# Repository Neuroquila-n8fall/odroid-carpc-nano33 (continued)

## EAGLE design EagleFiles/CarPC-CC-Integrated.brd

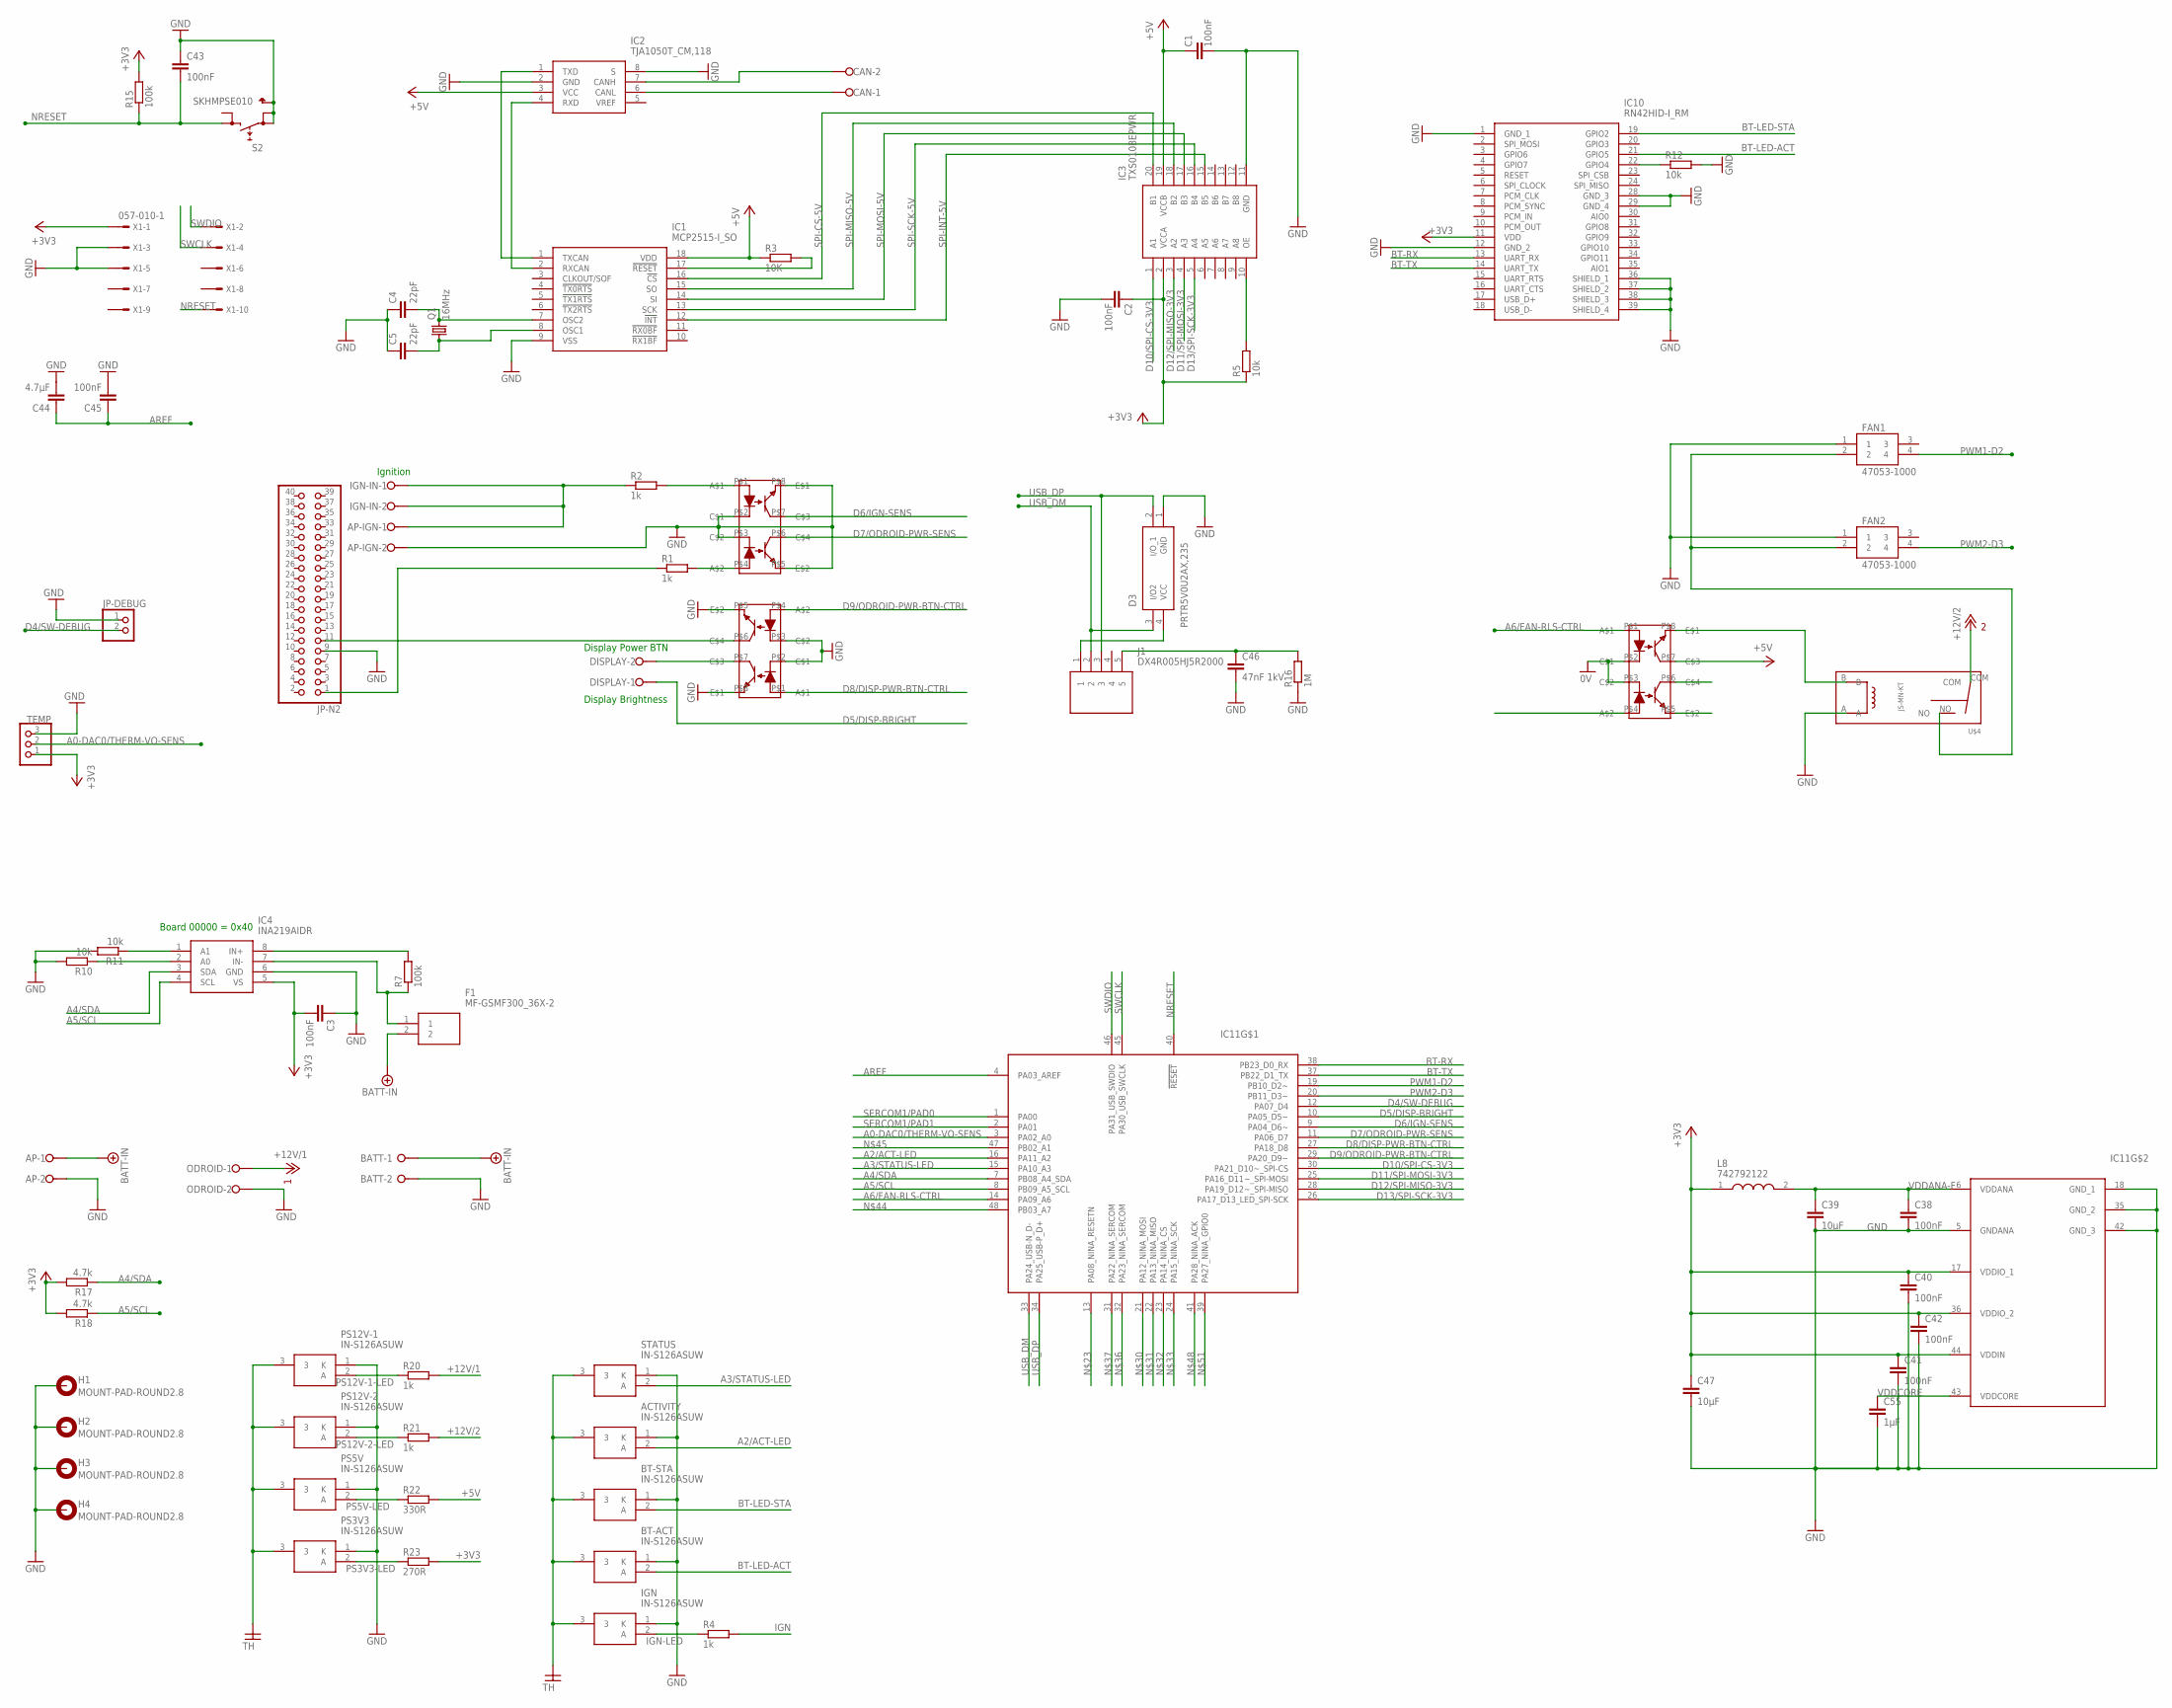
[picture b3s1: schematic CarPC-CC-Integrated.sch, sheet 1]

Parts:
ACTIVITY: IN-S126ASUW; INS126ASUW
AP: W237-02P; W237-132
AP-IGN: W237-02P; W237-132
BATT: W237-02P; W237-132
BT-ACT: IN-S126ASUW; INS126ASUW
BT-STA: IN-S126ASUW; INS126ASUW
C1, C2, C3, C38, C40, C41, C42, C43, C45: 100nF; C1206
C4, C5: 22pF; C1206
C39, C47: 10µF; C1206
C44: 4.7µF; C1206
C46: 47nF 1kV; C1206
C55: 1µF; C1206
CAN: W237-02P; W237-132
D3: PRTR5V0U2AX,235; PESD2ETHAXR
DISPLAY: W237-02P; W237-132
F1: MF-GSMF300_36X-2; MFGSMF30036X2
FAN1, FAN2: 47053-1000
H1, H2, H3, H4: MOUNT-PAD-ROUND2.8; 2,8-PAD
IC1: MCP2515-I_SO; SOIC127P1030X265-18N
IC2: TJA1050T_CM,118; SOIC127P600X175-8N
IC3: TXS0108EPWR; SOP65P640X120-20N
IC4: INA219AIDR; SOIC127P600X175-8N
IC10: RN42HID-I_RM; RN42HIDIRM
IC11: ATSAMD21G18A-AU-SPLIT; QFP50P900X900X120-48N
IGN: IN-S126ASUW; INS126ASUW
IGN-IN: W237-02P; W237-132
J1: DX4R005HJ5R2000; DX4R005HJ5
JP-DEBUG: PINHD-1X2; 1X02
JP-N2: PINHD-2X20; 2X20
L8: 742792122; INDC3216X130N
ODROID: W237-02P; W237-132
OK-FAN-CTRL: ILD74; FPR_ILD74
OK-PWR-IGN: ILD74; FPR_ILD74
OK-PWR-N2_DISP: ILD74; FPR_ILD74
PS3V3, PS5V, PS12V-1, PS12V-2: IN-S126ASUW; INS126ASUW
Q1: 16MHz; HC49/S
R1, R2, R4, R20, R21: 1k; R1206
R3: 10K; R1206
R5, R10, R11, R12: 10k; R1206
R7, R15: 100k; R1206
R16: 1M; R1206
R17, R18: 4.7k; R1206
R22: 330R; R1206
R23: 270R; R1206
S2: SKHMPSE010; SKHMPXE010
STATUS: IN-S126ASUW; INS126ASUW
TEMP: PINHD-1X3/90; 1X03/90
U$4: JS-MN-KT; FPR_JS-MN-KT
X1: 057-010-1

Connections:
0V: OK-FAN-CTRL.P$2, OK-FAN-CTRL.P$3
+3V3: C2.1, C3.2, C40.1, C41.1, C42.1, C47.1, IC3.2 (VCCA), IC4.5 (VS), IC10.11 (VDD), IC11.17 (VDDIO_1), IC11.36 (VDDIO_2), IC11.44 (VDDIN), L8.1, R5.1, R15.2, R17.2, R18.2, R23.2, TEMP.1, X1.1; also elsewhere on the board
+5V: C1.1, IC1.18 (VDD), IC2.3 (VCC), IC3.19 (VCCB), OK-FAN-CTRL.P$7, R3.1, R22.2; also elsewhere on the board
+12V/1: ODROID.1, R20.2; also elsewhere on the board
+12V/2: R21.2, U$4.COM; also elsewhere on the board
A0-DAC0/THERM-VO-SENS: IC11.3 (PA02_A0), TEMP.2
A2/ACT-LED: ACTIVITY.2 (A), IC11.16 (PA11_A2)
A3/STATUS-LED: IC11.15 (PA10_A3), STATUS.2 (A)
A4/SDA: IC4.3 (SDA), IC11.7 (PB08_A4_SDA), R17.1
A5/SCL: IC4.4 (SCL), IC11.8 (PB09_A5_SCL), R18.1
A6/FAN-RLS-CTRL: IC11.14 (PA09_A6), OK-FAN-CTRL.P$1
AREF: C44.1, C45.1, IC11.4 (PA03_AREF)
BATT-IN: AP.1, BATT.1, F1.2; also elsewhere on the board
BATT-IN-FUSED: F1.1, IC4.7 (IN-), R7.1
BT-ACTIVATE: IC10.22 (GPIO4), R12.1
BT-LED-ACT: BT-ACT.2 (A), IC10.21 (GPIO5)
BT-LED-STA: BT-STA.2 (A), IC10.19 (GPIO2)
BT-RX: IC10.13 (UART_RX), IC11.38 (PB23_D0_RX)
BT-TX: IC10.14 (UART_TX), IC11.37 (PB22_D1_TX)
CAN-H: CAN.2, IC2.7 (CANH)
CAN-L: CAN.1, IC2.6 (CANL)
D4/SW-DEBUG: IC11.12 (PA07_D4), JP-DEBUG.2
D5/DISP-BRIGHT: DISPLAY.1, IC11.10 (PA05_D5~)
D6/IGN-SENS: IC11.9 (PA04_D6~), OK-PWR-IGN.P$7
D7/ODROID-PWR-SENS: IC11.11 (PA06_D7), OK-PWR-IGN.P$6
D8/DISP-PWR-BTN-CTRL: IC11.27 (PA18_D8), OK-PWR-N2_DISP.P$1
D9/ODROID-PWR-BTN-CTRL: IC11.29 (PA20_D9~), OK-PWR-N2_DISP.P$4
D10/SPI-CS-3V3: IC3.1 (A1), IC11.30 (PA21_D10~_SPI-CS)
D11/SPI-MOSI-3V3: IC3.4 (A3), IC11.25 (PA16_D11~_SPI-MOSI)
D12/SPI-MISO-3V3: IC3.3 (A2), IC11.28 (PA19_D12~_SPI-MISO)
D13/SPI-SCK-3V3: IC3.5 (A4), IC11.26 (PA17_D13_LED_SPI-SCK)
DISP-PWR-BTN: DISPLAY.2, OK-PWR-N2_DISP.P$7
FAN-12V: FAN1.2, FAN2.2, U$4.NO
FAN-RLS-TRIG: OK-FAN-CTRL.P$8, U$4.B
GND: ACTIVITY.1 (K), AP.2, AP-IGN.2, BATT.2, BT-ACT.1 (K), BT-STA.1 (K), C1.2, C2.2, C3.1, C4.1, C5.1, C38.2, C39.2, C40.2, C41.2, C42.2, C43.1, C44.2, C45.2, C46.2, C47.2, C55.2, D3.1 (GND), FAN1.1, FAN2.1, H1.B2,8, H2.B2,8, H3.B2,8, H4.B2,8, IC1.9 (VSS), IC2.2 (GND), IC2.8 (S), IC3.11 (GND), IC4.6 (GND), IC10.1 (GND_1), IC10.12 (GND_2), IC10.28 (GND_3), IC10.29 (GND_4), IC10.36 (SHIELD_1), IC10.37 (SHIELD_2), IC10.38 (SHIELD_3), IC10.39 (SHIELD_4), IC11.5 (GNDANA), IC11.18 (GND_1), IC11.35 (GND_2), IC11.42 (GND_3), IGN.1 (K), JP-DEBUG.1, JP-N2.9, ODROID.2, OK-PWR-IGN.P$2, OK-PWR-IGN.P$3, OK-PWR-IGN.P$5, OK-PWR-IGN.P$8, OK-PWR-N2_DISP.P$2, OK-PWR-N2_DISP.P$3, OK-PWR-N2_DISP.P$5, OK-PWR-N2_DISP.P$8, PS3V3.1 (K), PS5V.1 (K), PS12V-1.1 (K), PS12V-2.1 (K), R10.2, R11.2, R12.2, R16.1, S2.1 (1.1), S2.2 (1.2), S2.5 (SH), STATUS.1 (K), TEMP.3, U$4.A, X1.3, X1.5; also elsewhere on the board
IGN: AP-IGN.1, IGN-IN.1, IGN-IN.2, R2.1, R4.2
IGN-IN: OK-PWR-IGN.P$1, R2.2
IGN-LED: IGN.2 (A), R4.1
INA-0X40-ADDR0: IC4.2 (A0), R10.1
INA-0X40-ADDR1: IC4.1 (A1), R11.1
MCP-OSC1: C5.2, IC1.8 (OSC1), Q1.1
MCP-OSC2: C4.2, IC1.7 (OSC2), Q1.2
MCP-RESET: IC1.17 (!RESET), R3.2
MCP-TJA-RX: IC1.2 (RXCAN), IC2.4 (RXD)
MCP-TJA-TX: IC1.1 (TXCAN), IC2.1 (TXD)
unnamed: D3.4 (VCC), J1.1
NRESET: C43.2, IC11.40 (!RESET), R15.1, S2.3 (2.1), X1.10
ODROID-3V3: JP-N2.1, R1.1
ODROID-3V3$2: OK-PWR-IGN.P$4, R1.2
ODROID-PWR-BTN: JP-N2.11, OK-PWR-N2_DISP.P$6
OE: IC3.10 (OE), R5.2
PS3V3-LED: PS3V3.2 (A), R23.1
PS5V-LED: PS5V.2 (A), R22.1
PS12V-1-LED: PS12V-1.2 (A), R20.1
PS12V-2-LED: PS12V-2.2 (A), R21.1
PWM1-D2: FAN1.4, IC11.19 (PB10_D2~)
PWM2-D3: FAN2.4, IC11.20 (PB11_D3~)
SERCOM1/PAD0: IC11.1 (PA00)
SERCOM1/PAD1: IC11.2 (PA01)
SHUNT+: IC4.8 (IN+), R7.2
SPI-CS-5V: IC1.16 (!CS), IC3.20 (B1)
SPI-INT-5V: IC1.12 (!INT), IC3.15 (B5)
SPI-MISO-5V: IC1.15 (SO), IC3.18 (B2)
SPI-MOSI-5V: IC1.14 (SI), IC3.17 (B3)
SPI-SCK-5V: IC1.13 (SCK), IC3.16 (B4)
SWCLK: IC11.45 (PA30_USB_SWCLK), X1.4
SWDIO: IC11.46 (PA31_USB_SWDIO), X1.2
TH: ACTIVITY.3, BT-ACT.3, BT-STA.3, IGN.3, PS3V3.3, PS5V.3, PS12V-1.3, PS12V-2.3, STATUS.3
USB-GND: C46.1, J1.5, R16.2
USB_DM: D3.3 (I/O2), IC11.33 (PA24_USB-N_D-), J1.2
USB_DP: D3.2 (I/O_1), IC11.34 (PA25_USB-P_D+), J1.3
VDDANA-F: C38.1, C39.1, IC11.6 (VDDANA), L8.2
VDDCORE: C55.1, IC11.43 (VDDCORE)

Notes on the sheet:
Ignition
Display Power BTN
Display Brightness
Board 00000 = 0x40

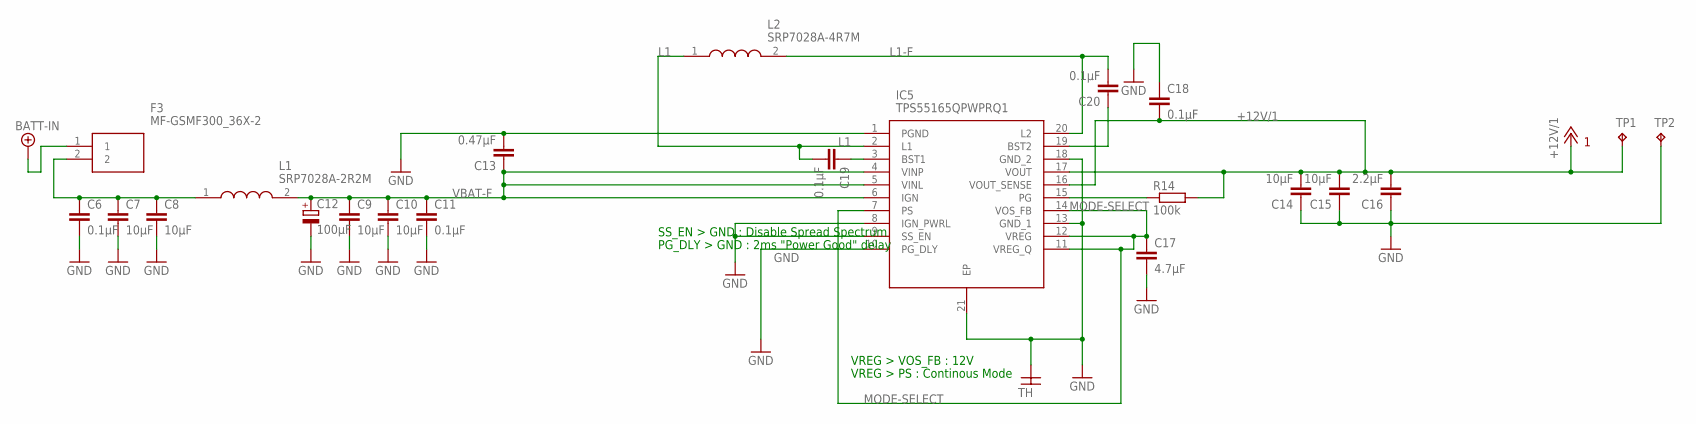
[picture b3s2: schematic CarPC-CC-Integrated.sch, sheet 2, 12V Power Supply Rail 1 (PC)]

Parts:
C6, C11, C18, C19, C20: 0.1µF; C1206
C7, C8, C9, C10, C14, C15: 10µF; C1206
C12: 100µF; SMC_B
C13: 0.47µF; C1206
C16: 2.2µF; C1206
C17: 4.7µF; C1206
F3: MF-GSMF300_36X-2; MFGSMF30036X2
IC5: TPS55165QPWPRQ1; SOP65P640X120-21N
L1: SRP7028A-2R2M; INDM7366X300N
L2: SRP7028A-4R7M; INDM7366X300N
R14: 100k; R1206
TP1, TP2: TPTP20R; TP20R

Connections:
+12V/1: C14.2, C15.2, C16.2, C18.2, IC5.16 (VOUT_SENSE), IC5.17 (VOUT), R14.2, TP1.TP; also elsewhere on the board
BATT-F: C6.1, C7.1, C8.1, F3.2, L1.1
BATT-IN: F3.1; also elsewhere on the board
BST1: C19.1, IC5.3 (BST1)
BST2: C20.1, IC5.19 (BST2)
GND: C6.2, C7.2, C8.2, C9.2, C10.2, C11.2, C12.-, C13.2, C14.1, C15.1, C16.1, C17.2, C18.1, IC5.1 (PGND), IC5.8 (IGN_PWRL), IC5.9 (SS_EN), IC5.10 (PG_DLY), IC5.13 (GND_1), IC5.18 (GND_2), IC5.21 (EP), TP2.TP; also elsewhere on the board
L1: C19.2, IC5.2 (L1), L2.1
L1-F: C20.2, IC5.20 (L2), L2.2
MODE-SELECT: C17.1, IC5.7 (PS), IC5.11 (VREG_Q), IC5.12 (VREG), IC5.14 (VOS_FB)
POWER-GOOD/1: IC5.15 (PG), R14.1
VBAT-F: C9.1, C10.1, C11.1, C12.+, C13.1, IC5.4 (VINP), IC5.5 (VINL), IC5.6 (IGN), L1.2

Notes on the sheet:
VREG > PS : Continous Mode
VREG > VOS_FB : 12V
SS_EN > GND : Disable Spread Spectrum
PG_DLY > GND : 2ms "Power Good" delay

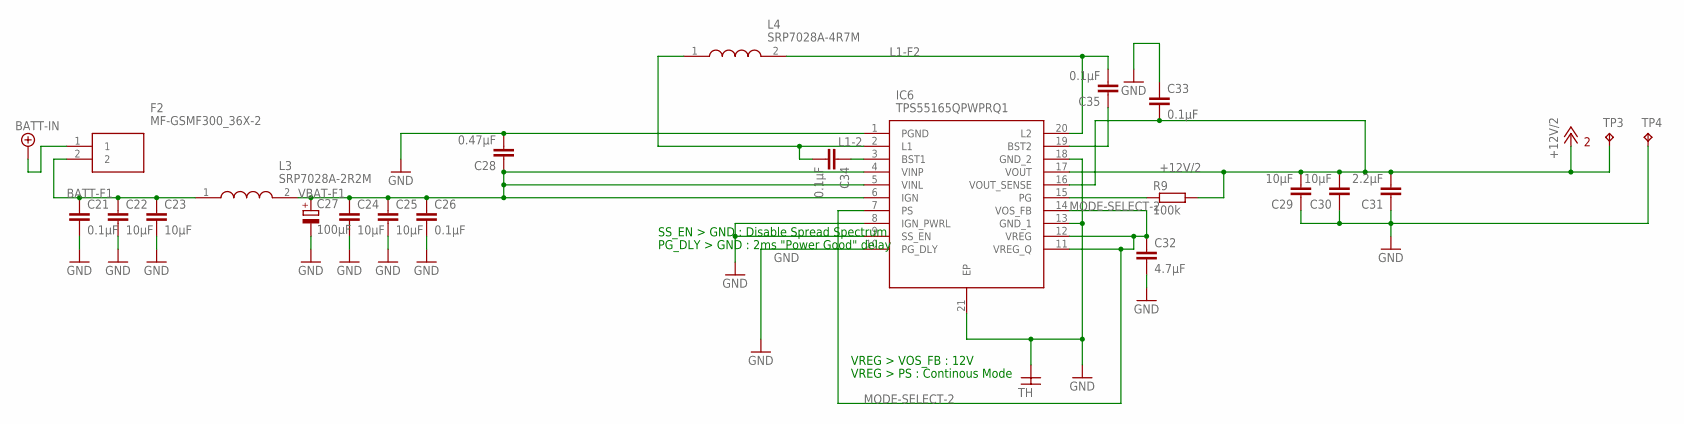
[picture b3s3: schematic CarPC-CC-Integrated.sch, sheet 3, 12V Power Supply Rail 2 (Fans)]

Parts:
C21, C26, C33, C34, C35: 0.1µF; C1206
C22, C23, C24, C25, C29, C30: 10µF; C1206
C27: 100µF; SMC_B
C28: 0.47µF; C1206
C31: 2.2µF; C1206
C32: 4.7µF; C1206
F2: MF-GSMF300_36X-2; MFGSMF30036X2
IC6: TPS55165QPWPRQ1; SOP65P640X120-21N
L3: SRP7028A-2R2M; INDM7366X300N
L4: SRP7028A-4R7M; INDM7366X300N
R9: 100k; R1206
TP3, TP4: TPTP20R; TP20R

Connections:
+12V/2: C29.2, C30.2, C31.2, C33.2, IC6.16 (VOUT_SENSE), IC6.17 (VOUT), R9.2, TP3.TP; also elsewhere on the board
BATT-F1: C21.1, C22.1, C23.1, F2.2, L3.1
BATT-IN: F2.1; also elsewhere on the board
BST1-2: C34.1, IC6.3 (BST1)
BST2-2: C35.1, IC6.19 (BST2)
GND: C21.2, C22.2, C23.2, C24.2, C25.2, C26.2, C27.-, C28.2, C29.1, C30.1, C31.1, C32.2, C33.1, IC6.1 (PGND), IC6.8 (IGN_PWRL), IC6.9 (SS_EN), IC6.10 (PG_DLY), IC6.13 (GND_1), IC6.18 (GND_2), IC6.21 (EP), TP4.TP; also elsewhere on the board
L1-2: C34.2, IC6.2 (L1), L4.1
L1-F2: C35.2, IC6.20 (L2), L4.2
MODE-SELECT-2: C32.1, IC6.7 (PS), IC6.11 (VREG_Q), IC6.12 (VREG), IC6.14 (VOS_FB)
POWER-GOOD/2: IC6.15 (PG), R9.1
VBAT-F1: C24.1, C25.1, C26.1, C27.+, C28.1, IC6.4 (VINP), IC6.5 (VINL), IC6.6 (IGN), L3.2

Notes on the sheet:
VREG > PS : Continous Mode
VREG > VOS_FB : 12V
SS_EN > GND : Disable Spread Spectrum
PG_DLY > GND : 2ms "Power Good" delay

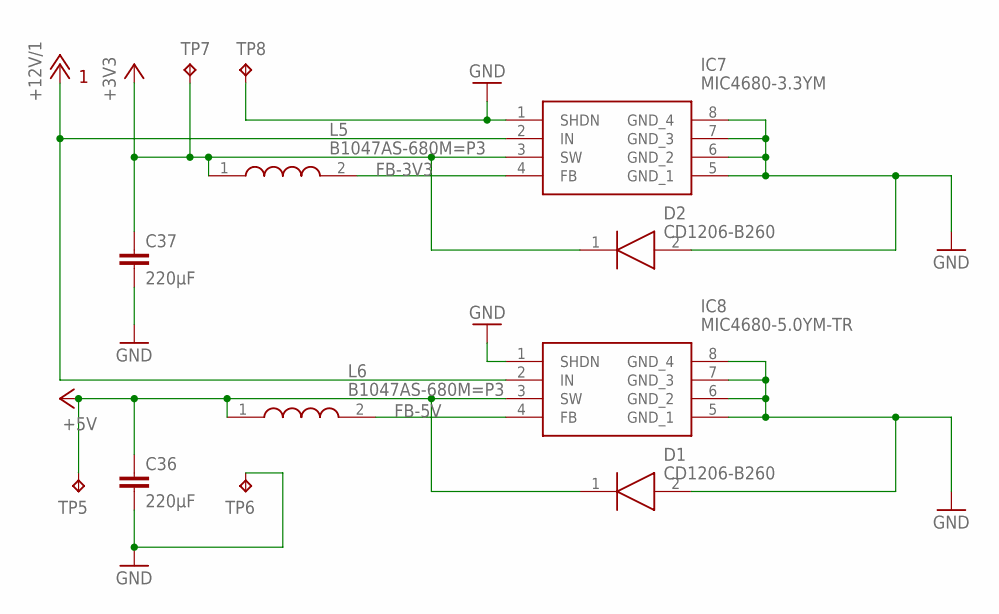
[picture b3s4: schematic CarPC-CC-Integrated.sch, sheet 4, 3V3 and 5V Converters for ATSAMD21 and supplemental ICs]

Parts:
C36, C37: 220µF; C1206
D1, D2: CD1206-B260; DIOC3419X116N
IC7: MIC4680-3.3YM; SOIC127P599X173-8N
IC8: MIC4680-5.0YM-TR; SOIC127P599X173-8N
L5, L6: B1047AS-680M=P3; INDPM7373X500N
TP5, TP6, TP7, TP8: TPTP20R; TP20R

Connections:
+3V3: C37.1, D2.1 (K), IC7.3 (SW), L5.1, TP7.TP; also elsewhere on the board
+5V: C36.1, D1.1 (K), IC8.3 (SW), L6.1, TP5.TP; also elsewhere on the board
+12V/1: IC7.2 (IN), IC8.2 (IN); also elsewhere on the board
FB-3V3: IC7.4 (FB), L5.2
FB-5V: IC8.4 (FB), L6.2
GND: C36.2, C37.2, D1.2 (A), D2.2 (A), IC7.1 (SHDN), IC7.5 (GND_1), IC7.6 (GND_2), IC7.7 (GND_3), IC7.8 (GND_4), IC8.1 (SHDN), IC8.5 (GND_1), IC8.6 (GND_2), IC8.7 (GND_3), IC8.8 (GND_4), TP6.TP, TP8.TP; also elsewhere on the board

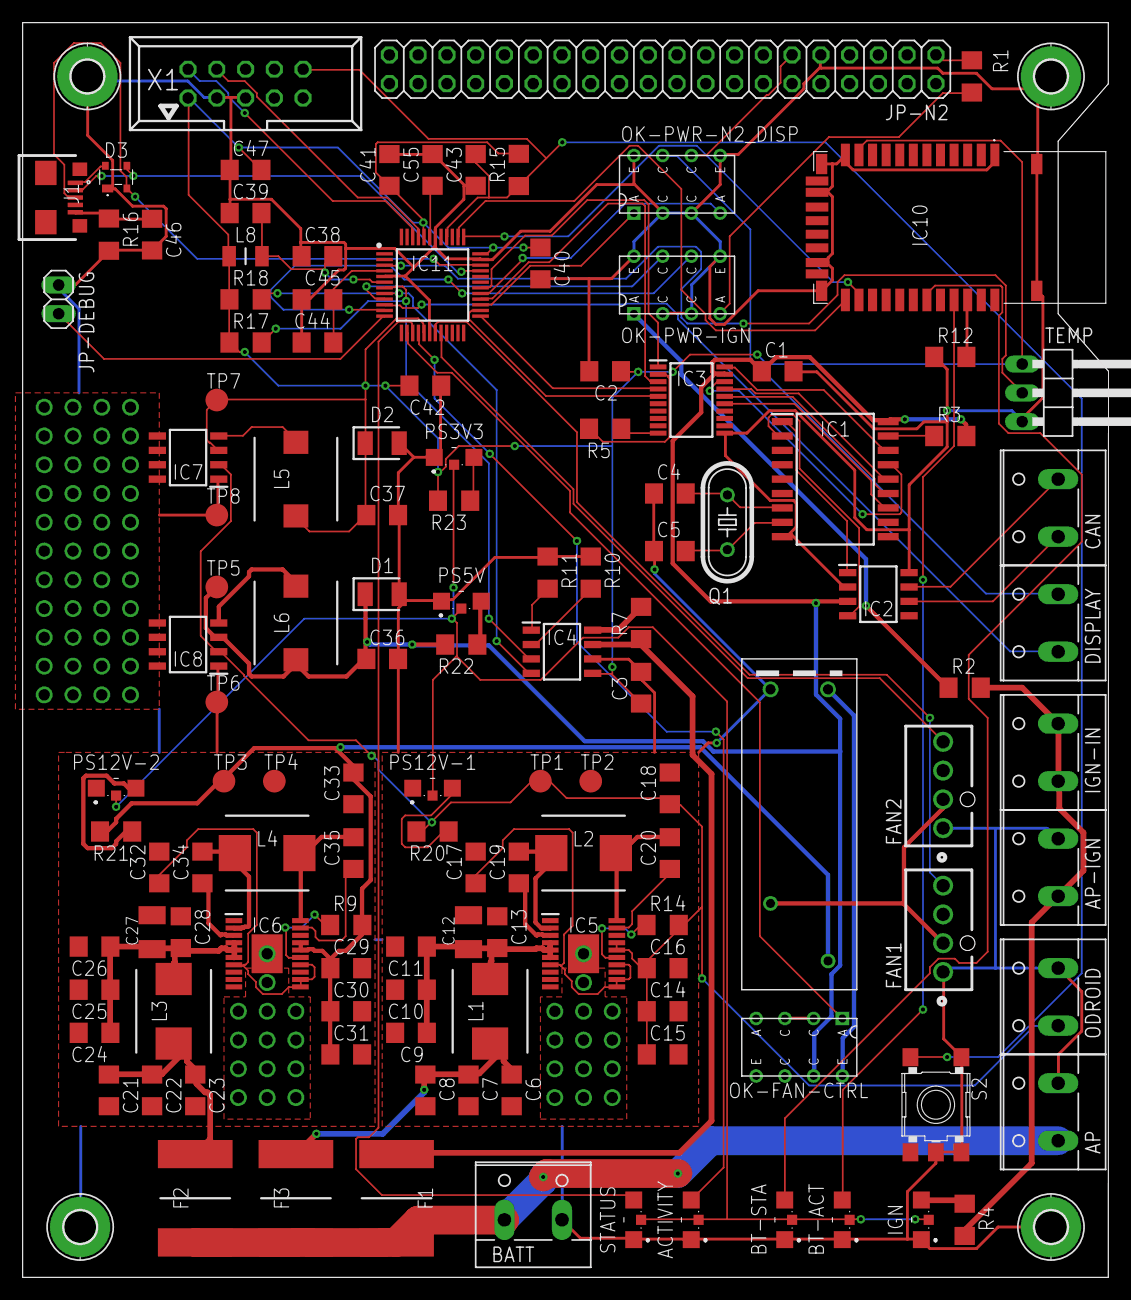
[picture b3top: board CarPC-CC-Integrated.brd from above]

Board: 2 copper layers, 95.9 x 110.8 mm, 131 parts (0 on the bottom side), 89 nets.

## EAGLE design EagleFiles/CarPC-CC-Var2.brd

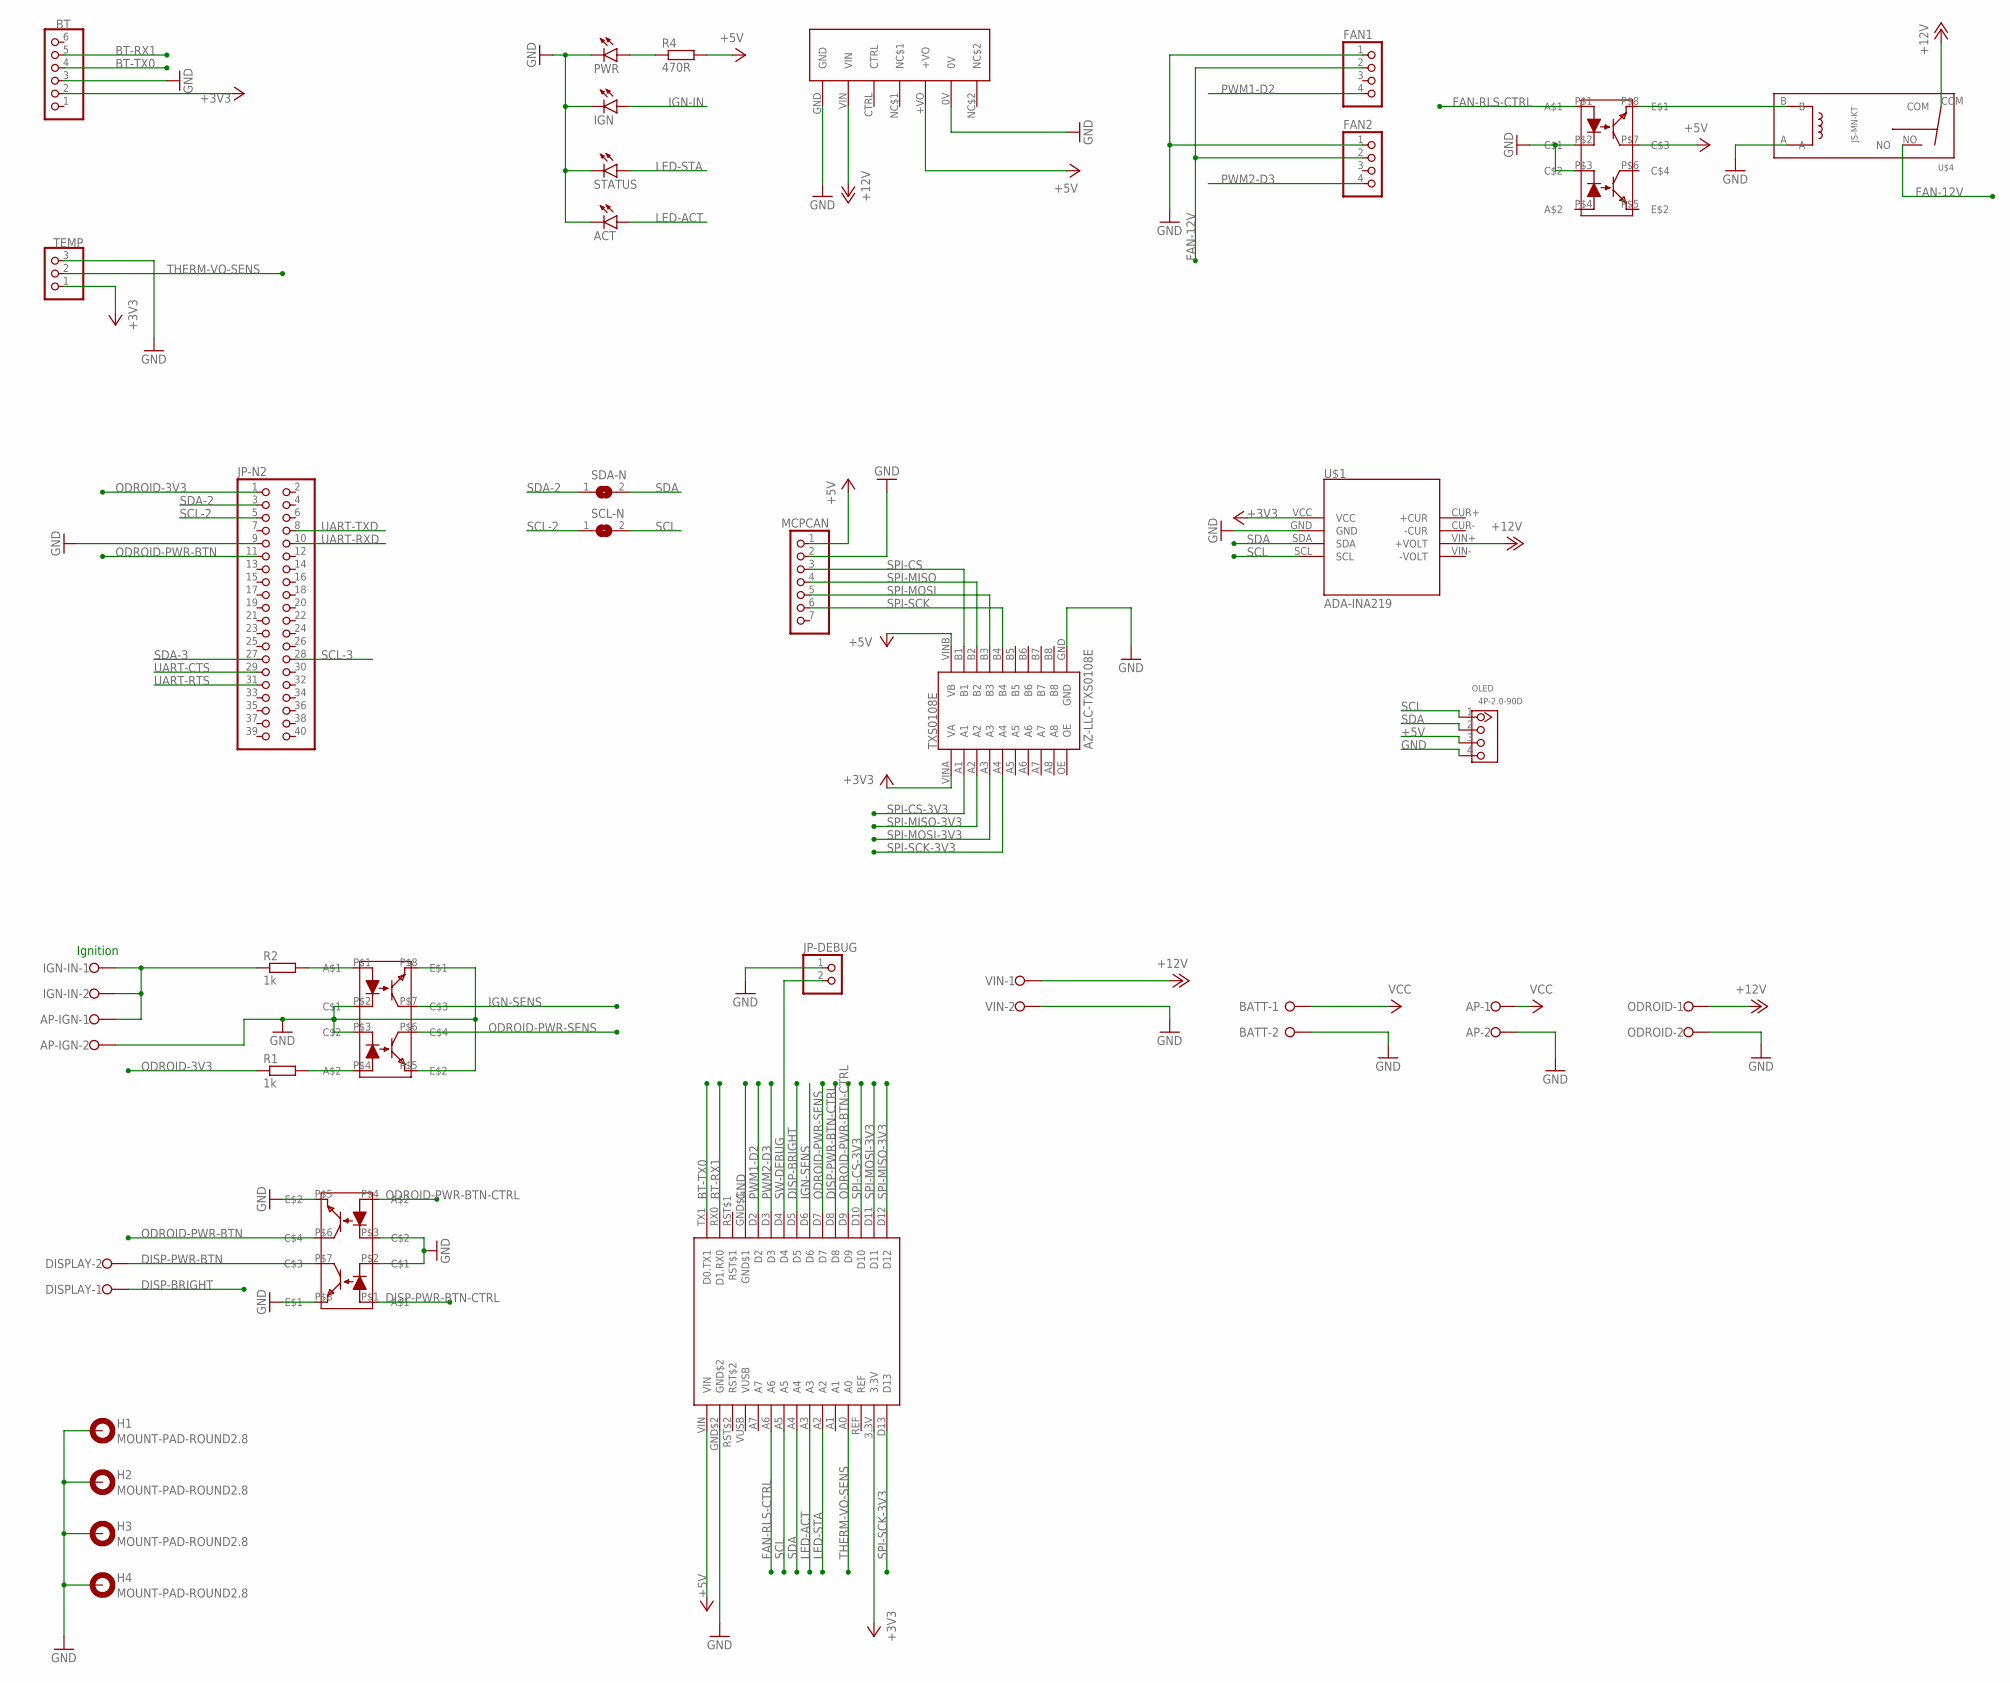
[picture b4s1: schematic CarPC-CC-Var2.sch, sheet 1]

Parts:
ACT: LED3MM
AP: W237-02P; W237-132
AP-IGN: W237-02P; W237-132
ARD-NANO-33-IOT: ARDUINONANO33IOT; FPR_ARDNANO33IOT
BATT: W237-02P; W237-132
BT: PINHD-1X6/90; 1X06/90
DISPLAY: W237-02P; W237-132
FAN1, FAN2: PINHD-1X4; 1X04
H1, H2, H3, H4: MOUNT-PAD-ROUND2.8; 2,8-PAD
IGN: LED3MM
IGN-IN: W237-02P; W237-132
JP-DEBUG: PINHD-1X2; 1X02
JP-N2: PINHD-2X20; 2X20
MCPCAN: PINHD-1X7/90; 1X07/90
ODROID: W237-02P; W237-132
OK-FAN-CTRL: ILD74; FPR_ILD74
OK-PWR-IGN: ILD74; FPR_ILD74
OK-PWR-N2_DISP: ILD74; FPR_ILD74
OLED: 4P-2.0-90D; HW4-2.0-90D
PWR: LED3MM
R1, R2: 1k; 0204/7
R4: 470R; 0204/7
SCL-N: SJ
SDA-N: SJ
STATUS: LED3MM
TEMP: PINHD-1X3/90; 1X03/90
TXS0108E: AZ-LLC-TXS0108E; FPR_LLC
U$1: ADA-INA219; FPR_INA219
U$3: 6S8W4_2405S1.6RP; PAC_6S8W4_2405S1.6RP
U$4: JS-MN-KT; FPR_JS-MN-KT
VIN: W237-02P; W237-132

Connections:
+3V3: ARD-NANO-33-IOT.3.3V, BT.2, TEMP.1, TXS0108E.VINA (VA), U$1.VCC
+5V: ARD-NANO-33-IOT.VIN, MCPCAN.1, OK-FAN-CTRL.P$7, OLED.3, R4.2, TXS0108E.VINB (VB), U$3.+VO
+12V: ODROID.1, U$1.VIN+ (+VOLT), U$3.VIN, U$4.COM, VIN.1
BT-RX1: ARD-NANO-33-IOT.RX0 (D1.RX0), BT.5
BT-TX0: ARD-NANO-33-IOT.TX1 (D0.TX1), BT.4
DISP-BRIGHT: ARD-NANO-33-IOT.D5, DISPLAY.1
DISP-PWR-BTN: DISPLAY.2, OK-PWR-N2_DISP.P$7
DISP-PWR-BTN-CTRL: ARD-NANO-33-IOT.D8, OK-PWR-N2_DISP.P$1
FAN-12V: FAN1.2, FAN2.2, U$4.NO
FAN-RLS-CTRL: ARD-NANO-33-IOT.A6, OK-FAN-CTRL.P$1
FAN-RLS-TRIG: OK-FAN-CTRL.P$8, U$4.B
GND: ACT.K (C), AP.2, AP-IGN.2, ARD-NANO-33-IOT.GND$1, ARD-NANO-33-IOT.GND$2, BATT.2, BT.3, FAN1.1, FAN2.1, H1.B2,8, H2.B2,8, H3.B2,8, H4.B2,8, IGN.K (C), JP-DEBUG.1, JP-N2.9, MCPCAN.2, ODROID.2, OK-FAN-CTRL.P$2, OK-FAN-CTRL.P$3, OK-PWR-IGN.P$2, OK-PWR-IGN.P$3, OK-PWR-IGN.P$5, OK-PWR-IGN.P$8, OK-PWR-N2_DISP.P$2, OK-PWR-N2_DISP.P$3, OK-PWR-N2_DISP.P$5, OK-PWR-N2_DISP.P$8, OLED.4, PWR.K (C), STATUS.K (C), TEMP.3, TXS0108E.GND, U$1.GND, U$3.0V, U$3.GND, U$4.A, VIN.2
IGN: AP-IGN.1, IGN-IN.1, IGN-IN.2, R2.1
IGN-IN: IGN.A, OK-PWR-IGN.P$1, R2.2
IGN-SENS: ARD-NANO-33-IOT.D6, OK-PWR-IGN.P$7
LED-ACT: ACT.A, ARD-NANO-33-IOT.A3
LED-PWR$1: PWR.A, R4.1
LED-STA: ARD-NANO-33-IOT.A2, STATUS.A
ODROID-3V3: JP-N2.1, R1.1
ODROID-3V3$2: OK-PWR-IGN.P$4, R1.2
ODROID-PWR-BTN: JP-N2.11, OK-PWR-N2_DISP.P$6
ODROID-PWR-BTN-CTRL: ARD-NANO-33-IOT.D9, OK-PWR-N2_DISP.P$4
ODROID-PWR-SENS: ARD-NANO-33-IOT.D7, OK-PWR-IGN.P$6
PWM1-D2: ARD-NANO-33-IOT.D2, FAN1.4
PWM2-D3: ARD-NANO-33-IOT.D3, FAN2.4
SCL: ARD-NANO-33-IOT.A5, OLED.1, SCL-N.2, U$1.SCL
SCL-2: JP-N2.5, SCL-N.1
SCL-3: JP-N2.28
SDA: ARD-NANO-33-IOT.A4, OLED.2, SDA-N.2, U$1.SDA
SDA-2: JP-N2.3, SDA-N.1
SDA-3: JP-N2.27
SPI-CS: MCPCAN.3, TXS0108E.B1
SPI-CS-3V3: ARD-NANO-33-IOT.D10, TXS0108E.A1
SPI-MISO: MCPCAN.4, TXS0108E.B2
SPI-MISO-3V3: ARD-NANO-33-IOT.D12, TXS0108E.A2
SPI-MOSI: MCPCAN.5, TXS0108E.B3
SPI-MOSI-3V3: ARD-NANO-33-IOT.D11, TXS0108E.A3
SPI-SCK: MCPCAN.6, TXS0108E.B4
SPI-SCK-3V3: ARD-NANO-33-IOT.D13, TXS0108E.A4
SW-DEBUG: ARD-NANO-33-IOT.D4, JP-DEBUG.2
THERM-VO-SENS: ARD-NANO-33-IOT.A0, TEMP.2
UART-CTS: JP-N2.29
UART-RTS: JP-N2.31
UART-RXD: JP-N2.10
UART-TXD: JP-N2.8
VCC: AP.1, BATT.1

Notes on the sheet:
Ignition

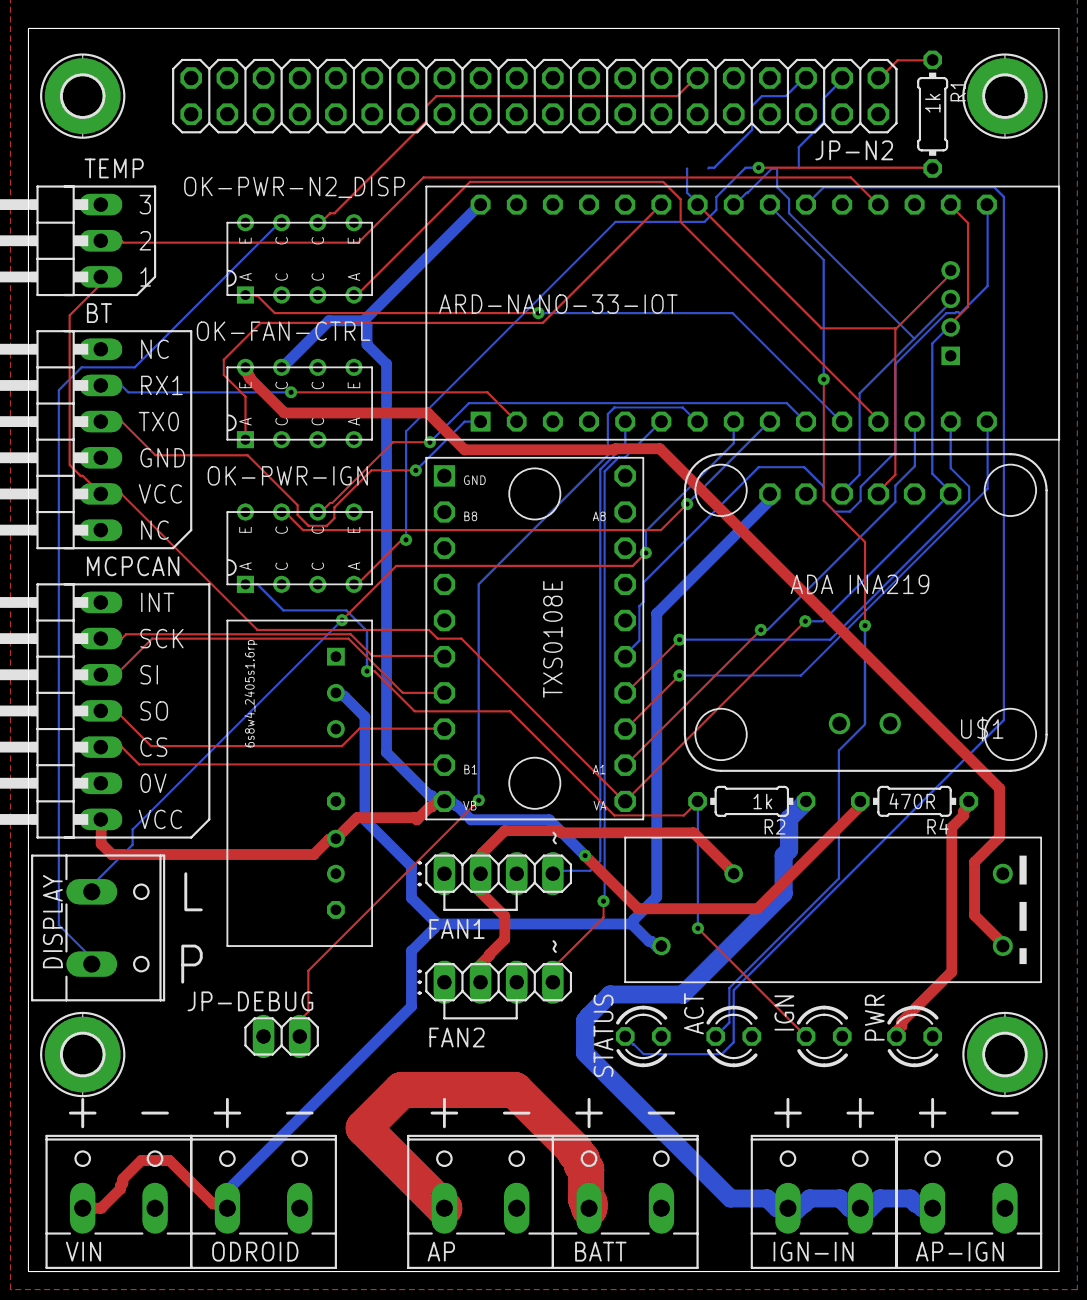
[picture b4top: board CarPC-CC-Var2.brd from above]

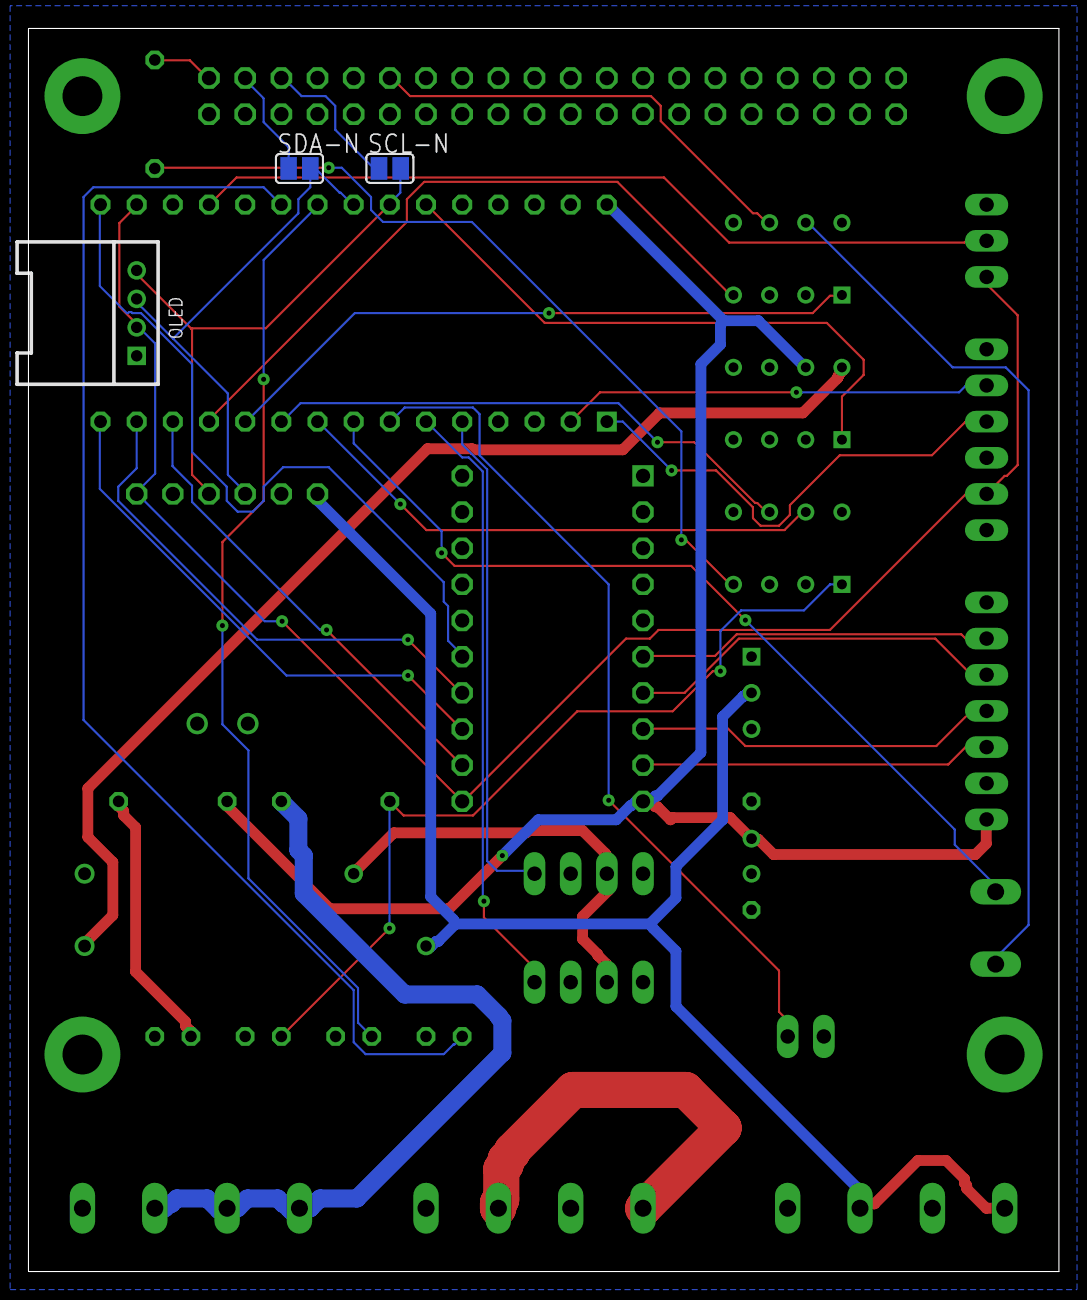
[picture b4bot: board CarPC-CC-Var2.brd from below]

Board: 2 copper layers, 72.4 x 87.3 mm, 36 parts (3 on the bottom side), 40 nets.

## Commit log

2020-01-02 Initial Commit - Clone of DUE Project
2020-01-02 Nano 33 IoT specific Libraries added
2020-01-03 Serial1 is on RX0, TX1 on the Nano 33 IoT
2020-01-04 Added PWM for FAN ctrl. Added LED Outputs
2020-01-17 Initial setup of all the bits involved
2020-01-17 Gitignore update
2020-01-17 Added schematics
2020-02-23 Cleanup & Bugfixes. Functionality 100% Completed
2020-02-23 Eagle Files updated to actual working copy
2020-02-23 Added Silkscreens for documentation
2020-02-23 Added Gerber & Production Files
2020-02-23 Wiring Diagram
2020-02-23 Readme Update: Introduced wiring explanation
    ...Still not complete...
2020-02-23 3D Images
2020-02-23 Additional 3d views
2020-02-23 Another Update of Readme
    Added additional information.
2020-02-23 I2C Info added
2020-02-23 I2C Info & Bottom view render
2020-02-24 Update README.md
    Typo
2020-02-24 Update README.md
    Added Info about LEDs and Diagnostics under "Signalling & Diagnostics"
2020-02-24 Update README.md
    More typos....
2020-02-24 Fixes to the BT setup routine.
2020-02-24 Error in schemic and board: using 5v rail now
2020-02-24 FIX: Swapped D9 with D8.
2020-02-25 Alternative Pin Assignments
2020-02-25 Debug Lichtwert
2020-02-28 Update README.md
    Documented F*ckups in the design.
2020-02-29 Fan control interferes with display brightness.
